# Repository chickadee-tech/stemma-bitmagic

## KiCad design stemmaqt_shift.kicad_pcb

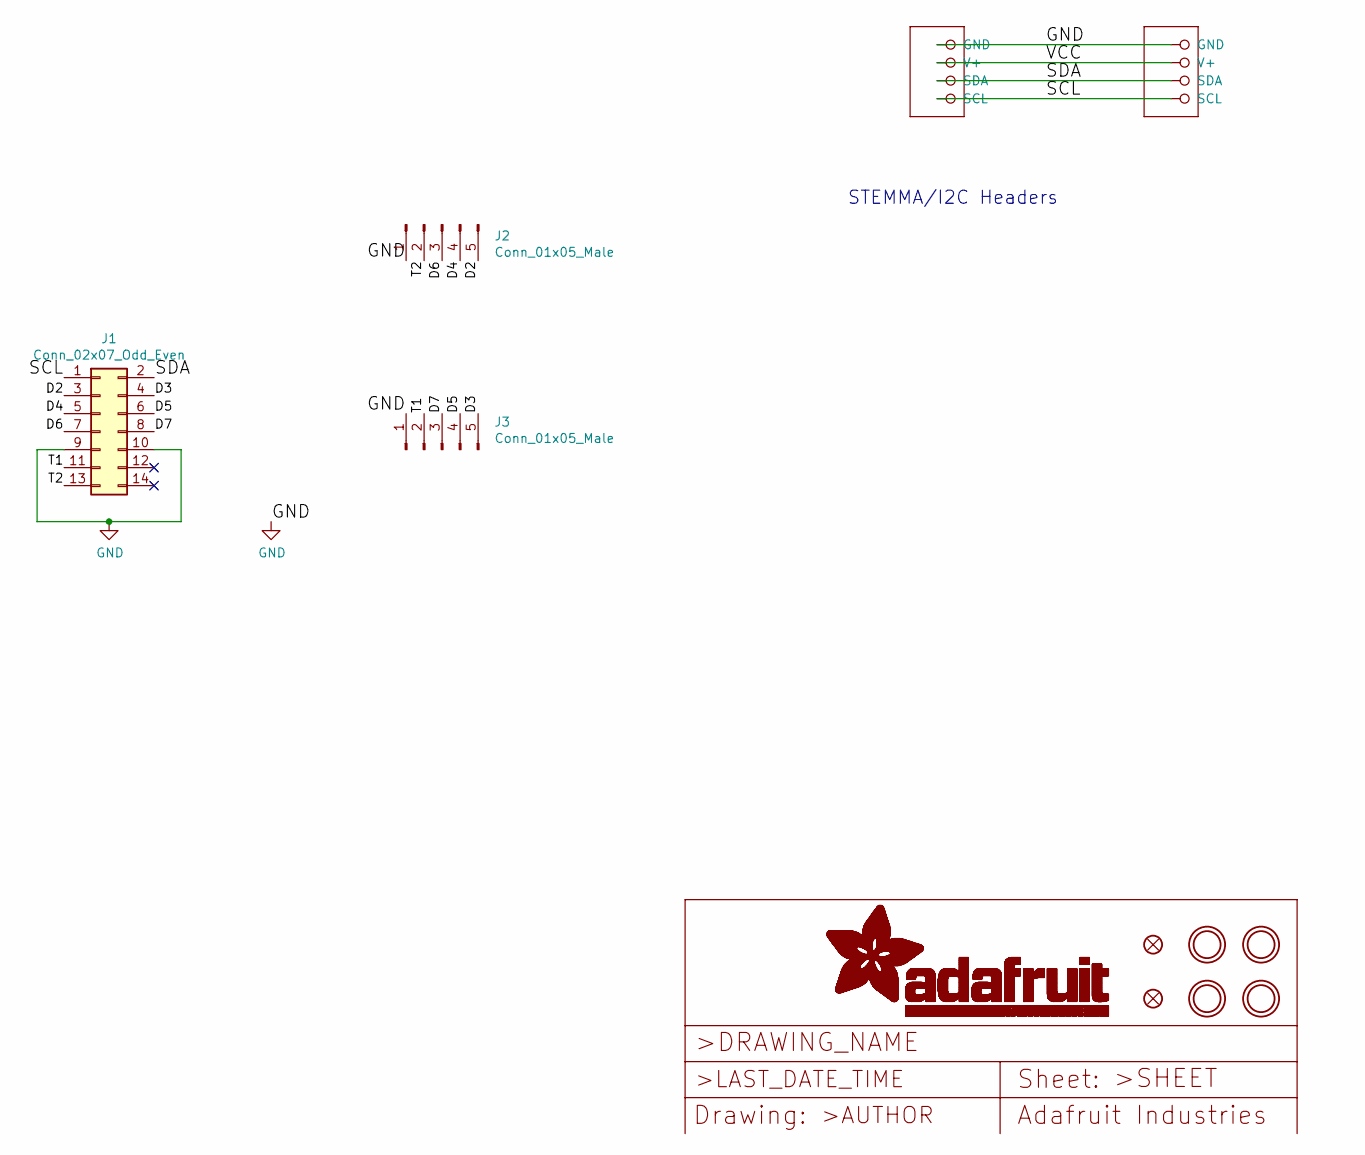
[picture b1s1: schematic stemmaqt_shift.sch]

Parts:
CONN3, CONN4: STEMMA_I2C_QT; JST_SH4
FID3, FID4: FIDUCIAL_1MM
J1: Conn_02x07_Odd_Even; PinHeader_2x07_P1.27mm_Vertical
J2, J3: Conn_01x05_Male; PinHeader_1x05_P2.54mm_Vertical
U$1, U$17, U$19, U$21: MOUNTINGHOLE2.5; MOUNTINGHOLE_2.5_PLATED

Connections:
/D2: J1.3, J2.5
/D3: J1.4, J3.5
/D4: J1.5, J2.4
/D5: J1.6, J3.4
/D6: J1.7, J2.3
/D7: J1.8, J3.3
/SCL: CONN3.4 (SCL), CONN4.4 (SCL), J1.1
/SDA: CONN3.3 (SDA), CONN4.3 (SDA), J1.2
/T1: J1.11, J3.2
/T2: J1.13, J2.2
/VCC: CONN3.2 (V+), CONN4.2 (V+)
GND: CONN3.1 (GND), CONN4.1 (GND), J1.9, J1.10, J2.1, J3.1

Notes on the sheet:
STEMMA/I2C Headers

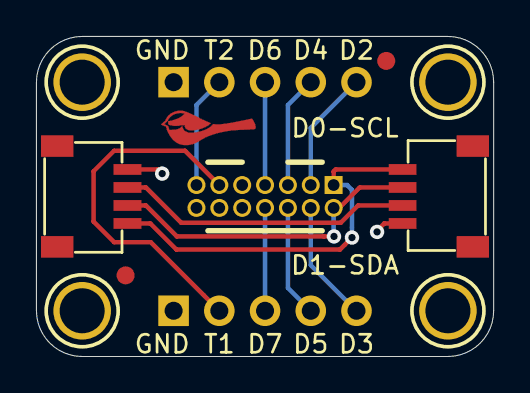
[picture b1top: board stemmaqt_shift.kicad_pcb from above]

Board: 2 copper layers, 25.4 x 17.8 mm, 15 parts (0 on the bottom side), 12 nets.

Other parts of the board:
U$22: ADAFRUIT_3.5MM
U$25: PCBFEAT-REV-040
U$30, U$31: STEMMAQT

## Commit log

2019-10-01 First rev of stemma bitmagic
